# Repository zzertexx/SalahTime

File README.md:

# SalahTime
Device that shows prayer time and Qibla direction anywhere & anytime without any internet connection

## What is it?
It is an ESP32-powered device with buttons, GNSS receiver, RTC, magnetic sensor, and E-Paper display. By using all of these, it is planned to show prayer time using latitude and longitude alongside with direction to Qibla by magnetic sensor. Because there is an E-Paper display, battery can last for many-many days. If the battery will be drained, it is easy to charge using universal Type-C port. Currently, it shows prayer time based on location, but will have full interface and direction to Qibla in the future.

## Why did I build it?
I was walking in Shenzhen after Fallout with my phone died and then realized that I have to read Salah
I could not know if the next salah already started and I needed the direction to Qibla
Strangers there do not understand English, so I could not communicate with them
Then, I got an idea of internet-free device that can predict prayer time and show the direction to Qibla

## Steps to Reproduce
1. Order PCB and parts from any provider(Example: JLCPCB)
2. Assemble and solder parts to PCB
3. 3D Print CAD models from "CAD" folder
4. Push software into MCU and download required libraries using Arduino IDE 
5. Use!

## Arduino IDE Libraries:
GxEPD2
TinyGPS++
RTClib

## Bill of Materials
| Name | Quantity | Price |
| --- | --- | --- |
| DS3231M RTC | 1 | 3.25$ |
| ATGM336H GNSS | 1 | 2.22$ |
| ESP32-C3FH4 | 1 | 2.18$ |
| Vibration Motor | 1 | 0.56$ |
| Tactile Push Buttons | 5 | 0.3$ |
| Ceramic Active Antenna | 1 | 0.73$ |
| Coin Cell Holder | 1 | 1.27$ |
| MAX17048 fuel gauges | 1 | 2.18$ |
| ME6211 LDO to 3.3v | 1 | 0.52$ |
| NPN Transistor | 1 | 0.02$ |
| 2.9-inch E Ink Display | 1 | 4$ |
| 803040 1000 mAh LiPo | 1 | 4$ |
| Type-C 8 Pin | 1 | 0.04$ |
| 2.5mm JST Connector | 1 | 0.04$ |
| SI1308EDL N-MOSFET | 1 | 0.1$ |
| TP4056 | 1 | 0.2$ |
| FS8205A | 1 | 0.05$ |
| DW01A | 1 | 0.5$ |
| E Ink connector | 1 | 0.11$ |
| QST QMC5883P | 1 | 1.6$ | 
| 0,1uF C | 6 | 0.2$ |
| 10uF | 3 | 0.2$ | 
| 1uF/25V | 14 | 0.7$ |
| 4.7uF/25V | 3 | 0.2$ |
| 15pF | 2 | 0.03$ |
| 10nF | 1 | 0.02$ |
| THT 3mm diodes | 2 | 0.07$ |
| MBR0530 Diode | 3 | 0.02$ |
| 47nH L | 1 | 0,06$ |
| 47uH L | 1 | 0.08$ |
| 2nH L | 1 | 0.01$ |
| 10K R | 1 | 0.01$ |
| 1K R | 4 | 0.01$ |
| 1.2K R | 1 | 0.05$ |
| 4.7K R | 2 | 0.07$ |
| 100 R | 1 | 0.01$ |
| 1M R | 1 | 0.01$ |
| 2.2 R | 1 | 0.01$ |
| 499 R | 1 | 0.01$ |
| 0 R | 1 | 0.01$ |
| 10pF Crystal | 1 | 0.3$ | 
| TOTAL: | 26$ |

## Images

[schematics.pdf](https://github.com/user-attachments/files/32201017/schematics.pdf)

## AI DISCLOSURE
AI was used to search components and to write computing algorithm

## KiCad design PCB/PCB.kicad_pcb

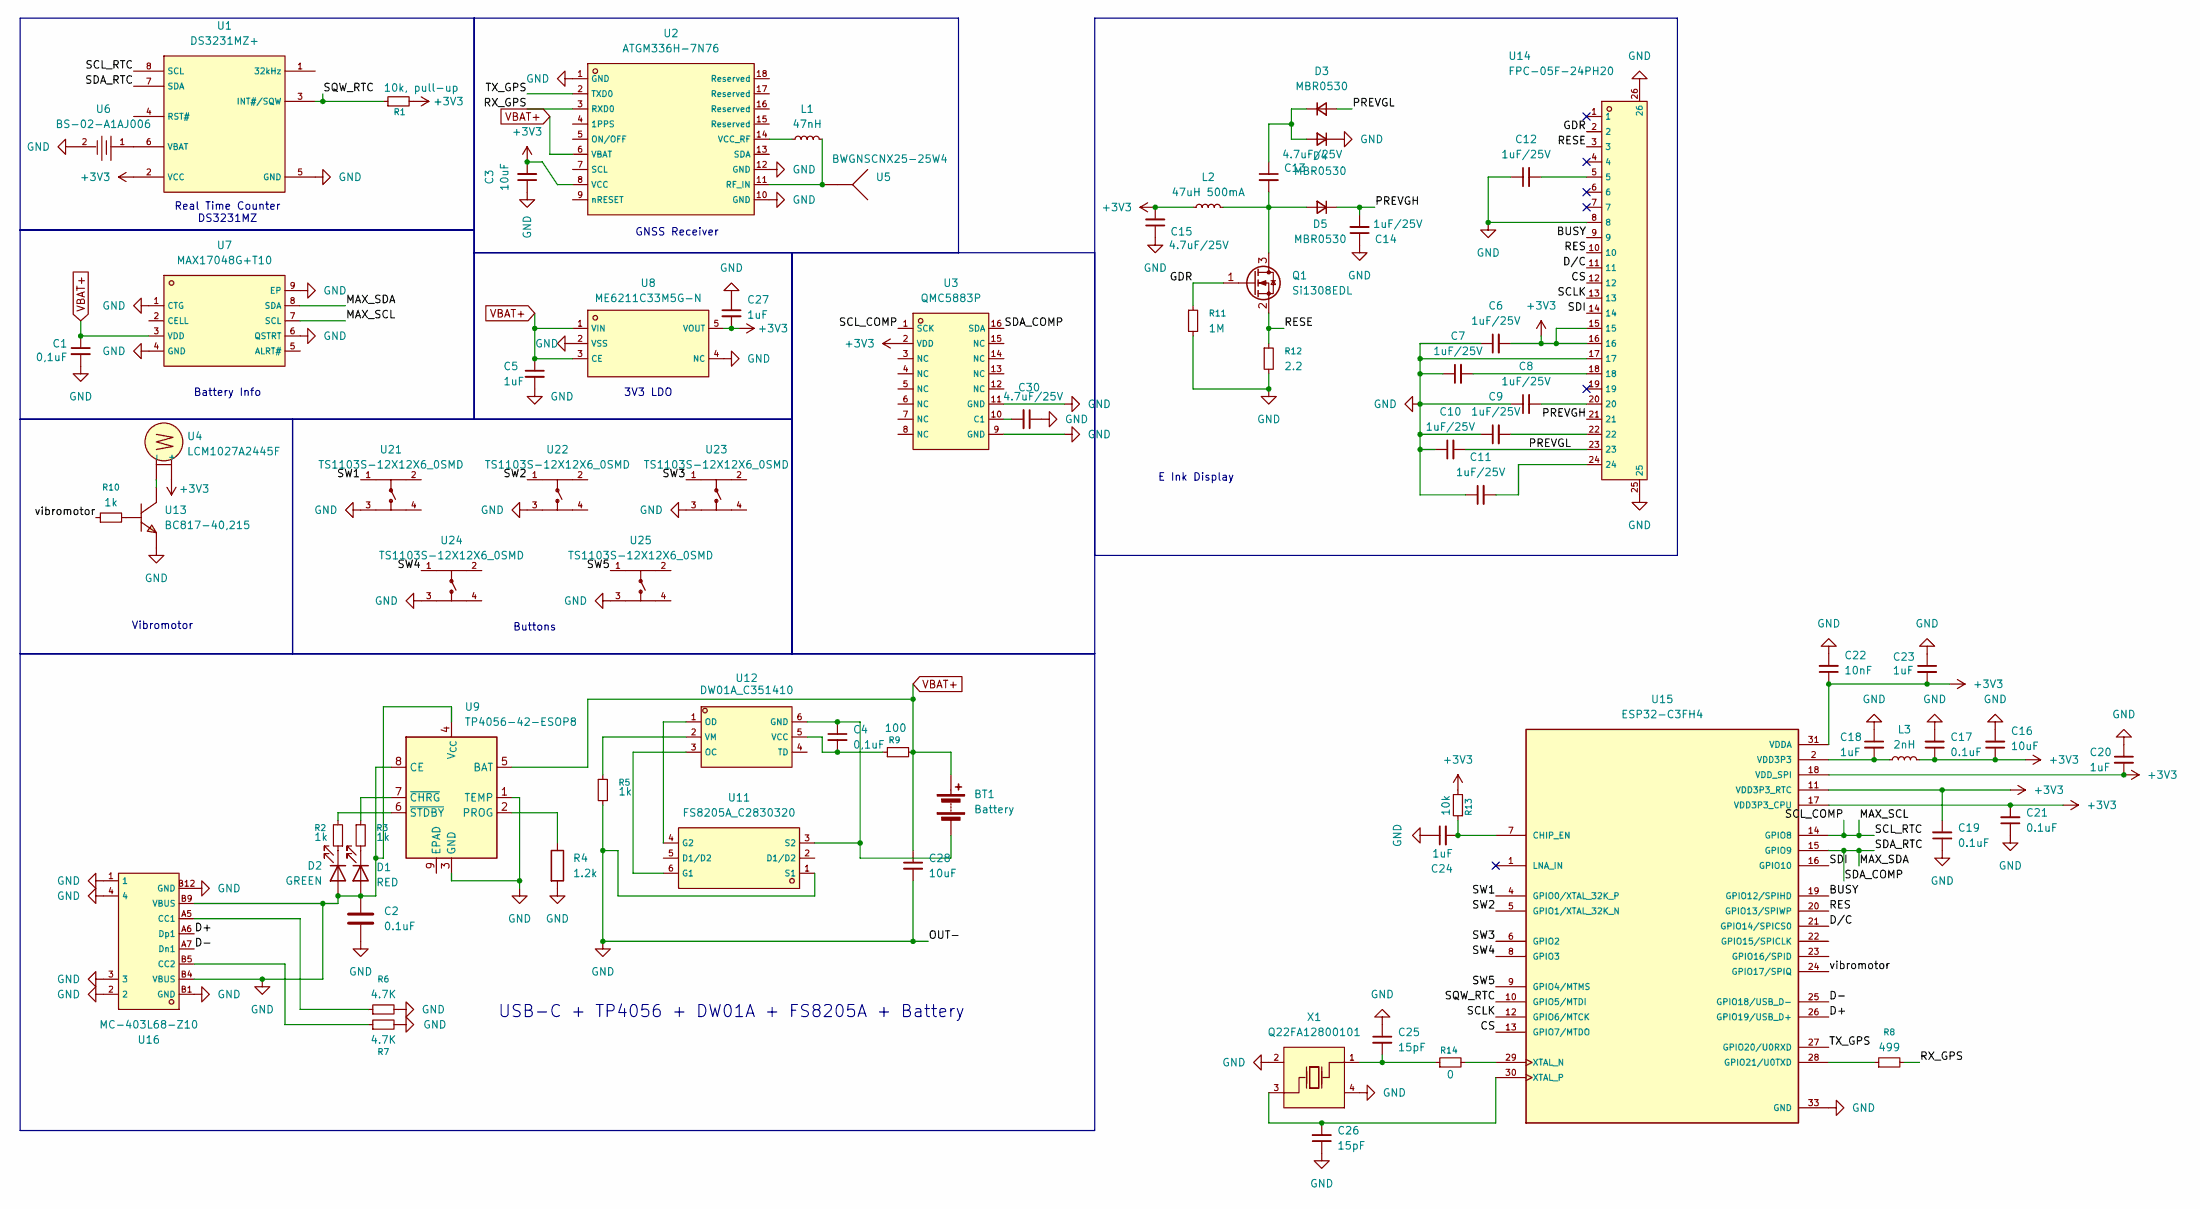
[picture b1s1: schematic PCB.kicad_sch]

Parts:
BT1: Battery; CONN-TH_S2B-XH-A-LF-SN
C1, C4: 0,1uF; C_0805_2012Metric_Pad1.18x1.45mm_HandSolder
C2, C17, C19, C21: 0.1uF; C_0805_2012Metric_Pad1.18x1.45mm_HandSolder
C3, C16, C28: 10uF; C_0805_2012Metric_Pad1.18x1.45mm_HandSolder
C5, C18, C20, C23, C24, C27: 1uF; C_0805_2012Metric_Pad1.18x1.45mm_HandSolder
C6, C7, C8, C9, C10, C11, C12, C14: 1uF/25V; C_0805_2012Metric_Pad1.18x1.45mm_HandSolder
C13, C15, C30: 4.7uF/25V; C_0805_2012Metric_Pad1.18x1.45mm_HandSolder
C22: 10nF; C_0603_1608Metric_Pad1.08x0.95mm_HandSolder
C25, C26: 15pF; C_0603_1608Metric_Pad1.08x0.95mm_HandSolder
D1: RED; LED_D3.0mm
D2: GREEN; LED_D3.0mm
D3, D4, D5: MBR0530; SOD-123_L2.7-W1.6-LS3.7-RD-1
L1: 47nH; L_0402_1005Metric_Pad0.77x0.64mm_HandSolder
L2: 47uH 500mA; IND-SMD_L4.0-W4.0_FNR40XXS
L3: 2nH; L_0603_1608Metric_Pad1.05x0.95mm_HandSolder
Q1: Si1308EDL; SOT-323_SC-70
R1: 10k, pull-up; R_0603_1608Metric_Pad0.98x0.95mm_HandSolder
R2, R3, R5, R10: 1k; R_0603_1608Metric_Pad0.98x0.95mm_HandSolder
R4: 1.2k; R_0603_1608Metric_Pad0.98x0.95mm_HandSolder
R6, R7: 4.7K; R_0603_1608Metric_Pad0.98x0.95mm_HandSolder
R8: 499; R_0603_1608Metric_Pad0.98x0.95mm_HandSolder
R9: 100; R_0805_2012Metric_Pad1.20x1.40mm_HandSolder
R11: 1M; R_0603_1608Metric_Pad0.98x0.95mm_HandSolder
R12: 2.2; R_0603_1608Metric_Pad0.98x0.95mm_HandSolder
R13: 10k; R_0603_1608Metric_Pad0.98x0.95mm_HandSolder
R14: 0; R_0603_1608Metric_Pad0.98x0.95mm_HandSolder
U1: DS3231MZ+; SOIC-8_L4.9-W3.9-P1.27-LS6.0-BL; LCSC C107410
U2: ATGM336H-7N76; COMM-SMD_18P-L10.1-W9.7-P1.1-TL_L76-LB; LCSC C53325902
U3: QMC5883P; LGA-16_L3.0-W3.0-P0.50-BL_SQ; LCSC C2847467
U4: LCM1027A2445F; VIBRATING-MOTOR-SMD_WELDING; LCSC C2759984
U5: BWGNSCNX25-25W4; ANT-TH_L25.0-W25.0; LCSC C784398
U6: BS-02-A1AJ006; BAT-TH_MYOUNG_BS-02-A1AJ006; LCSC C964745
U7: MAX17048G+T10; TDFN-8_L2.0-W2.0-P0.50-BL-EP1.2; LCSC C2682616
U8: ME6211C33M5G-N; SOT-23-5_L3.0-W1.7-P0.95-LS2.8-BL; LCSC C82942
U9: TP4056-42-ESOP8; SOIC-8-1EP_3.9x4.9mm_P1.27mm_EP2.41x3.3mm_ThermalVias
U11: FS8205A_C2830320; SOT-23-6_L2.9-W1.6-P0.95-LS2.8-BR; LCSC C2830320
U12: DW01A_C351410; SOT-23-6_L2.9-W1.6-P0.95-LS2.8-BL; LCSC C351410
U13: BC817-40,215; SOT-23-3_L2.9-W1.6-P1.90-LS2.8-BR; LCSC C52801
U14: FPC-05F-24PH20; FPC-SMD_24P-P0.50_FPC-05F-24PH20; LCSC C2856805
U15: ESP32-C3FH4; QFN50P500X500X90-33N; PARTREV 2.0
U16: MC-403L68-Z10; USB-TYPE-C-SMD_MC-403L68-Z10; LCSC C47326496
U21, U22, U23, U24, U25: TS1103S-12X12X6_0SMD; SW-SMD_4P-L12.0-W12.0-P5.00-LS15.5; LCSC C48677734
X1: Q22FA12800101; CRYSTAL-SMD_4P-L2.0-W1.6-BL; LCSC C255898

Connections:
+3V3: C3.2, C6.2, C15.2, C16.1, C17.1, C19.2, C20.2, C21.2, C22.1, C23.2, C27.2, L2.1, L3.2, R1.2, R13.2, U1.2 (VCC), U2.8 (VCC), U3.2 (VDD), U4.2 (+), U8.5 (VOUT), U14.15, U14.16, U15.11 (VDD3P3_RTC), U15.17 (VDD3P3_CPU), U15.18 (VDD_SPI), U15.31 (VDDA), U15.32 (VDDA)
/BUSY: U14.9, U15.19 (GPIO12/SPIHD)
/CS: U14.12, U15.13 (GPIO7/MTDO)
/D+: U15.26 (GPIO19/USB_D+), U16.A6 (Dp1)
/D-: U15.25 (GPIO18/USB_D-), U16.A7 (Dn1)
/D/C: U14.11, U15.21 (GPIO14/SPICS0)
/GDR: Q1.1 (G), R11.1, U14.2
/MAX_SCL: U1.8 (SCL), U3.1 (SCK), U7.7 (SCL), U15.14 (GPIO8)
/MAX_SDA: U1.7 (SDA), U3.16 (SDA), U7.8 (SDA), U15.15 (GPIO9)
/PREVGH: C14.2, D5.1 (K), U14.21
/PREVGL: C10.2, D3.2 (A), U14.23
/RES: U14.10, U15.20 (GPIO13/SPIWP)
/RESE: Q1.2 (S), R12.1, U14.3
/RX_GPS: R8.2, U2.3 (RXD0)
/SCLK: U14.13, U15.12 (GPIO6/MTCK)
/SDI: U14.14, U15.16 (GPIO10)
/SQW_RTC: R1.1, U1.3 (INT#/SQW), U15.10 (GPIO5/MTDI)
/SW1: U15.4 (GPIO0/XTAL_32K_P), U21.1
/SW2: U15.5 (GPIO1/XTAL_32K_N), U22.1
/SW3: U15.6 (GPIO2), U23.1
/SW4: U15.8 (GPIO3), U24.1
/SW5: U15.9 (GPIO4/MTMS), U25.1
/TX_GPS: U2.2 (TXD0), U15.27 (GPIO20/U0RXD)
/vibromotor: R10.1, U15.24 (GPIO17/SPIQ)
GND: C1.2, C2.1, C2.2, C3.1, C5.2, C6.1, C7.1, C8.1, C9.1, C10.1, C11.1, C12.1, C14.1, C15.1, C16.2, C17.2, C18.1, C19.1, C20.1, C21.1, C22.2, C23.1, C24.1, C25.1, C26.1, C27.1, C28.2, C30.1, D1.2 (A), D2.2 (A), D4.1 (K), R4.2, R5.2, R6.2, R7.2, R11.2, R12.2, U1.5 (GND), U2.1 (GND), U2.10 (GND), U2.12 (GND), U3.9 (GND), U3.11 (GND), U6.2, U7.1 (CTG), U7.4 (GND), U7.6 (QSTRT), U7.9 (EP), U8.2 (VSS), U8.4 (NC), U9.1 (TEMP), U9.3 (GND), U9.4 (V_{CC}), U9.8 (CE), U11.1 (S1), U13.2, U14.8, U14.17, U14.25, U14.26, U15.33 (GND), U16.1, U16.2, U16.3, U16.4, U16.B1 (GND), U16.B4 (VBUS), U16.B9 (VBUS), U16.B12 (GND), U21.3, U22.3, U23.3, U24.3, U25.3, X1.2, X1.4
unnamed: BT1.2 (-), C4.1, U11.3 (S2), U12.6 (GND)
unnamed: C7.2, U14.18
unnamed: C8.2, U14.20
unnamed: C9.2, U14.22
unnamed: C11.2, U14.24
unnamed: C12.2, U14.5
unnamed: D1.1 (K), R3.2
unnamed: D2.1 (K), R2.1
unnamed: C13.1, D3.1 (K), D4.2 (A)
unnamed: C13.2, D5.2 (A), L2.2, Q1.3 (D)
unnamed: R10.2, U13.1
unnamed: U1.6 (VBAT), U6.1
unnamed: L1.2, U2.11 (RF_IN), U5.1 (ANT_1)
unnamed: L1.1, U2.14 (VCC_RF)
unnamed: C30.2, U3.10 (C1)
unnamed: U4.1 (-), U13.3
unnamed: R4.1, U9.2 (PROG)
unnamed: R3.1, U9.7 (~CHRG)
unnamed: R2.2, U9.6 (~STDBY)
unnamed: U11.6 (G1), U12.3 (OC)
unnamed: U11.4 (G2), U12.1 (OD)
unnamed: C4.2, R9.1, U12.5 (VCC)
unnamed: R5.1, U12.2 (VM)
unnamed: C24.2, R13.1, U15.7 (CHIP_EN)
unnamed: R8.1, U15.28 (GPIO21/U0TXD)
unnamed: R14.2, U15.29 (XTAL_N)
unnamed: C26.2, U15.30 (XTAL_P), X1.3 (OSC2)
unnamed: R6.1, U16.A5 (CC1)
unnamed: R7.1, U16.B5 (CC2)
unnamed: C25.2, R14.1, X1.1 (OSC1)
VBAT+: BT1.1 (+), C1.1, C5.1, C28.1, R9.2, U2.6 (VBAT), U7.3 (VDD), U8.1 (VIN), U8.3 (CE), U9.5 (BAT)
VDD3P3: C18.2, L3.1, U15.2 (VDD3P3), U15.3 (VDD3P3)

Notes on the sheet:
3V3 LDO
Battery Info
Buttons
GNSS Receiver
Real Time Counter DS3231MZ
USB-C + TP4056 + DW01A + FS8205A + Battery
E Ink Display
Vibromotor

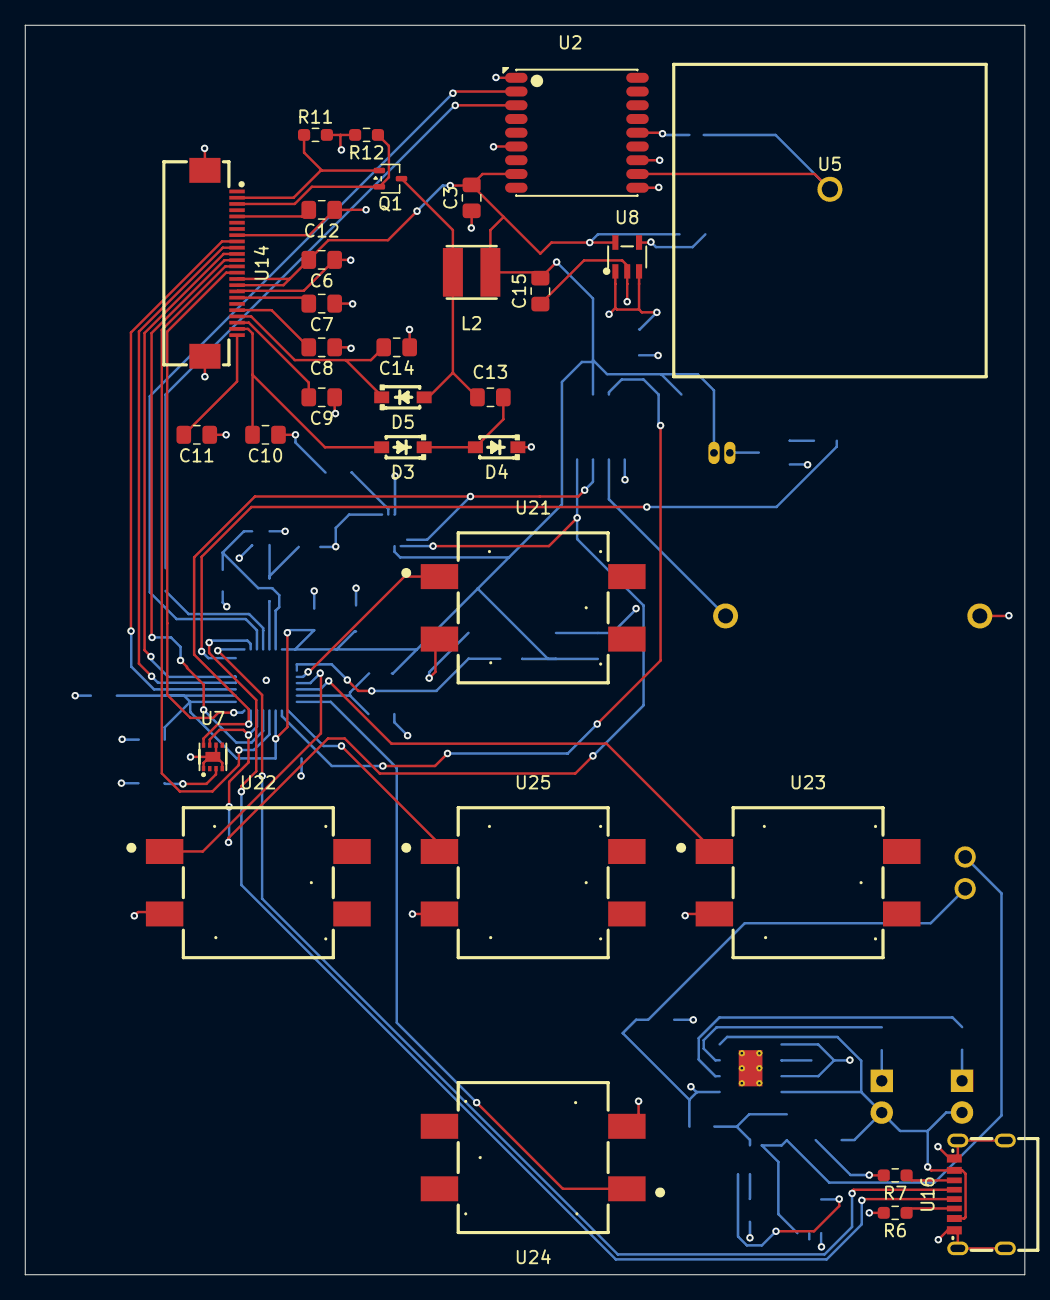
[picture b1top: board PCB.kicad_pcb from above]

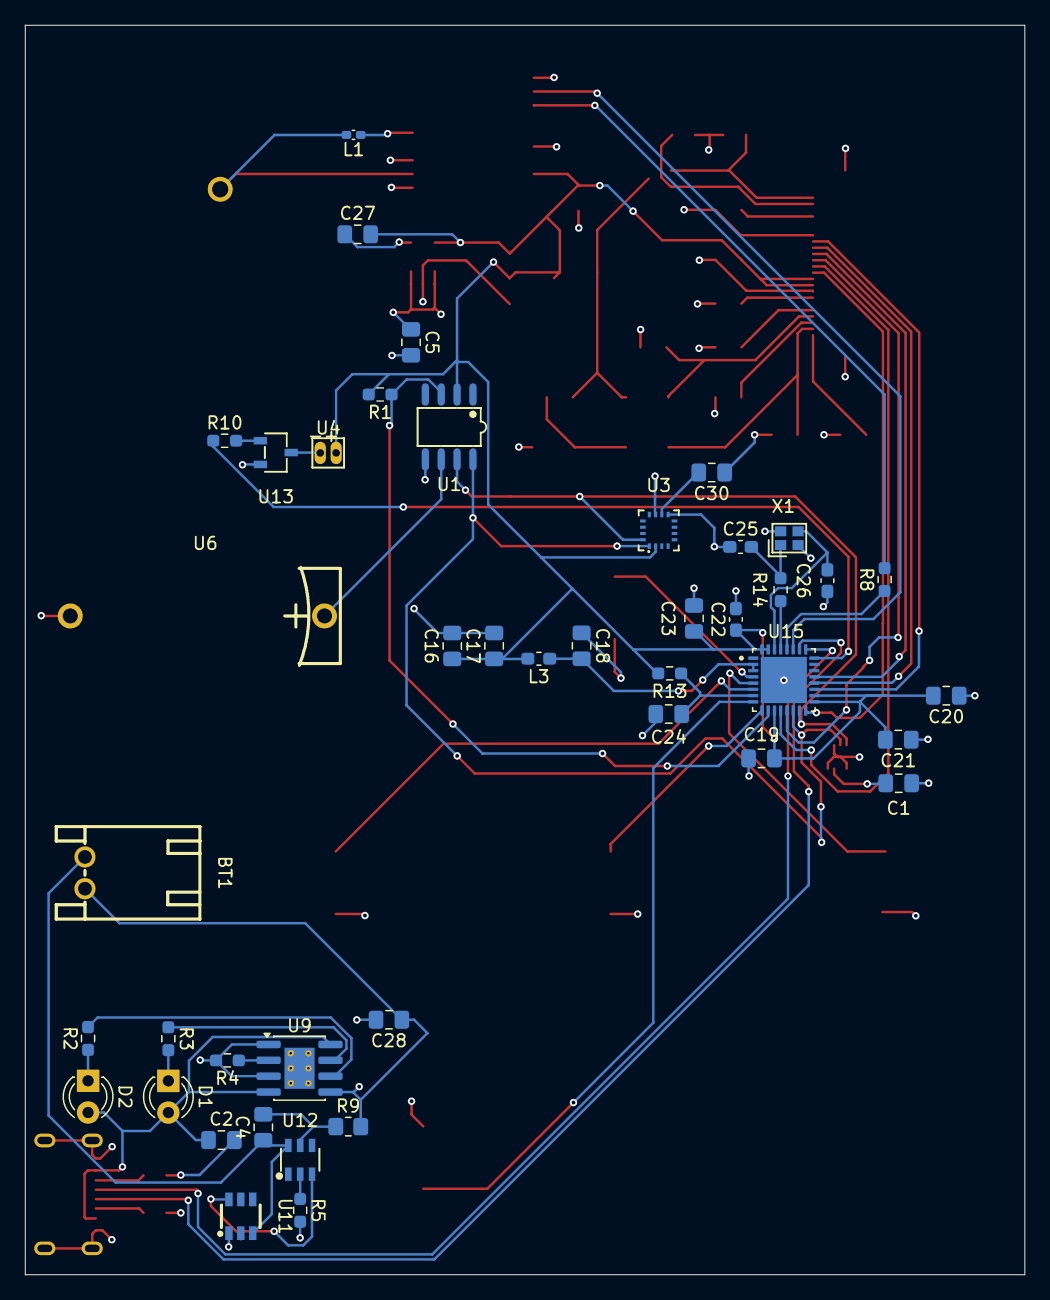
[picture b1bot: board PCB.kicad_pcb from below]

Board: 4 copper layers, 80.0 x 100.0 mm, 74 parts (43 on the bottom side), 57 nets.

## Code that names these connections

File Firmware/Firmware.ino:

#include <Wire.h>
#include <RTClib.h>
#include <TinyGPS++.h>
#include <GxEPD2_BW.h>
#include <Fonts/FreeMonoBold9pt7b.h>
#include <Preferences.h>
#include <math.h>

#define DEG2RAD(d) ((d) * M_PI / 180.0) 
#define RAD2DEG(r) ((r) * 180.0 / M_PI)

#define SW1 4
#define SW2 5
#define SW3 6
#define SW4 8
#define SW5 9
#define SQW_RTC 10  // INT#/SQW on DS3231
#define SCLK 12     // SCLK on E Ink screen connector
#define CS 13       // CS on E Ink screen connector
#define I2C_SCL 14
#define I2C_SDA 15
#define SDI 16         // SDI on E Ink screen
#define BUSY 19        // BUSY on E Ink screen
#define RES 20         // RES on E Ink screen
#define DC 21          // DC on E Ink screen
#define vibromotor 24  // base on transistor
#define TX_GPS 27
#define RX_GPS 28

const double FAJR_ANGLE = 18.0;
const double ISHA_ANGLE = 18.0;
const double ASR_FACTOR = 2;

struct PrayerTimes {
  double fajr, sunrise, dhuhr, asr, maghrib, isha;
};

double julianDay(int year, int month, int day) {
  if(month <= 2) { 
    year -= 1;
    month += 12;
  }
  int A = year / 100;
  int B = 2 - A + (A / 4);
  return floor(365.25 * (year + 4716)) + floor(30.6001 * (month + 1)) + day + B - 1524.5;
}

void sunPosition(double jd, double &declination, double &eqTimeMinutes) {
  double D = jd - 2451545.0;
  double g = fmod(357.529 + 0.98560028 * D, 360.0);
  double q = fmod(280.459 + 0.98564736 * D, 360.0);
  double L = fmod(q + 1.915 * sin(DEG2RAD(g)) + 0.020 * sin(DEG2RAD(2 * g)), 360.0);

  double e = 23.439 - 0.00000036 * D;

  double RA = RAD2DEG(atan2(cos(DEG2RAD(e)) * sin(DEG2RAD(L)), cos(DEG2RAD(L)))) / 15.0;
  RA = fmod(RA, 24.0);
  if (RA < 0) RA += 24.0; 

  declination = RAD2DEG(asin(sin(DEG2RAD(e)) * sin(DEG2RAD(L))));

  double eqTimeHours = (q / 15.0) - RA;

  if(eqTimeHours > 12) eqTimeHours -= 24;
  if(eqTimeHours < -12) eqTimeHours += 24;
  eqTimeMinutes = eqTimeHours * 60.0;
}

double hourAngle(double angle, double latitude, double declination) {
  double lat = DEG2RAD(latitude);
  double decl = DEG2RAD(declination);
  double a = DEG2RAD(angle);

  double cosH = (-sin(a) - sin(lat) * sin(decl)) / (cos(lat) * cos(decl));

  if (cosH > 1.0) cosH = 1.0;
  if (cosH < -1.0) cosH = -1.0;

  return RAD2DEG(acos(cosH)) / 15.0;
}

double asrHourAngle(double factor, double latitude, double declination) {
  double lat = DEG2RAD(latitude);
  double decl = DEG2RAD(declination);

  double a = -atan(1.0 / (factor + tan(fabs(lat - decl))));
  double cosH = (sin(a) - sin(lat) * sin(decl)) / (cos(lat) * cos(decl));

  if (cosH > 1.0) cosH = 1.0;
  if (cosH < -1.0) cosH = -1.0;

  return RAD2DEG(acos(cosH)) / 15.0;
}

PrayerTimes calculatePrayerTimes(int year, int month, int day, double latitude, double longitude, double timeZoneOffsetHours) {
  double jd = julianDay(year, month, day);

  double declination, eqTimeMinutes;
  sunPosition(jd, declination, eqTimeMinutes);
  double eqTimeHours = eqTimeMinutes / 60.0;

  double dhuhr = 12.0 + timeZoneOffsetHours - (longitude / 15.0) - eqTimeHours;

  double sunHA = hourAngle(0.833, latitude, declination);
  double fajrHA = hourAngle(FAJR_ANGLE, latitude, declination);
  double ishaHA = hourAngle(ISHA_ANGLE, latitude, declination);
  double asrHA = asrHourAngle(ASR_FACTOR, latitude, declination);

  PrayerTimes t;
  t.fajr = dhuhr - fajrHA;
  t.sunrise = dhuhr - sunHA;
  t.dhuhr = dhuhr;
  t.asr = dhuhr + asrHA;
  t.maghrib = dhuhr + sunHA;
  t.isha = dhuhr + ishaHA;

  return t;
}

void printTime(double decimalHours, char* buf, size_t bufSize) {
  if (decimalHours < 0) decimalHours += 24;
  if (decimalHours >= 24) decimalHours -= 24;
  int h = (int)decimalHours;
  int m = (int)round((decimalHours - h) * 60);
  if (m == 60) { m = 0; h += 1; }
  snprintf(buf, bufSize, "%02d:%02d", h, m);
}

// Objects
RTC_DS3231 rtc; // create an object "rtc" of type "RTC_DS3231"
TinyGPSPlus gps;
HardwareSerial gpsSerial(1);
Preferences prefs;

GxEPD2_BW<GxEPD2_290_T5, GxEPD2_290_T5::HEIGHT> display(
  GxEPD2_290_T5(CS, DC, RES, BUSY)
);

bool coldStart = false;

void showStatus(const char* msg) {
  display.setFullWindow();
  display.firstPage();
  do {
    display.fillScreen(GxEPD_WHITE);
    display.setCursor(10, 30);
    display.print(msg);
  } while (display.nextPage());
}

void acquireGpsFixBlocking() {
  unsigned long start = millis();
  bool locked = false;

  while(!locked) {
    while(gpsSerial.available() > 0) {
      gps.encode(gpsSerial.read());
    }

    if(gps.location.isValid() && gps.date.isValid() && gps.time.isValid()) {
      locked = true;

      double lat = gps.location.lat();
      double lng = gps.location.lng();

      rtc.adjust(DateTime(gps.date.year(), gps.date.month(), gps.date.day(), 
                          gps.time.hour(), gps.time.minute(), gps.time.second()));

      prefs.putFloat("lat", lat);
      prefs.putFloat("lng", lng);
      prefs.putBool("setup_done", true);

      Serial.printf("GPS Lock: %.6f, %.6f\n", lat, lng);
      showStatus("GPS Locked!");
      delay(1000);
    }

    if(millis() - start > 300000UL) {
      showStatus("No GPS fix. \nCheck sky view");
      delay(3000);
      start = millis();
    }
  }
}

void setup() {
  Serial.begin(115200);

  // Buttons as inputs
  pinMode(SW1, INPUT_PULLUP);
  pinMode(SW2, INPUT_PULLUP);
  pinMode(SW3, INPUT_PULLUP);
  pinMode(SW4, INPUT_PULLUP);
  pinMode(SW5, INPUT_PULLUP);

  // Vibration + short boot buzz
  pinMode(vibromotor, OUTPUT);
  digitalWrite(vibromotor, HIGH);
  delay(150);
  digitalWrite(vibromotor, LOW);

  // Screen on
  display.init(115200);
  display.setRotation(1);
  display.setFont(&FreeMonoBold9pt7b);
  display.setTextColor(GxEPD_BLACK);
  showStatus("Booting...");

  // I2C + RTC
  Wire.begin(I2C_SDA, I2C_SCL);
  pinMode(SQW_RTC, INPUT_PULLUP);

  if(!rtc.begin()) {
    Serial.println("DS3231 is not recognized!");
    showStatus("ERROR: RTC not found");
  }

  // NVS
  prefs.begin("salahtracker", false); // open a non-dependend on power memory inside of ESP32, false = write allowed
  bool setupComplete = prefs.getBool("setup_done", false);

  // Determine cold start
  bool timeInvalid = rtc.lostPower(); // true if the module lost power since the last check
  bool locationInvalid = !setupComplete;

  if(timeInvalid || locationInvalid){
    coldStart = true;
    Serial.println("COLD START - GPS FIX REQUIRED");
    showStatus("First time setup...\nSearching for GPS");
  } else {
    DateTime now = rtc.now();
    Serial.printf("Current RTC time is: %04d-%02d-%02d %02d:%02d\n", 
                    now.year(), now.month(), now.day(), now.hour(), now.minute());
  }

  gpsSerial.begin(9600, SERIAL_8N1, RX_GPS, TX_GPS);

  if(coldStart) {
    acquireGpsFixBlocking();
  }
  
  double tz = 5.0; // UTC +5

  PrayerTimes pt = calculatePrayerTimes(now.year(), now.month(), now.day(), lat, lng, tz);

  char fajrBuf[6], dhuhrBuf[6], asrBuf[6], maghribBuf[6], ishaBuf[6];
  printTime(pt.fajr, fajrBuf, sizeof(fajrBuf));
  printTime(pt.dhuhr, dhuhrBuf, sizeof(dhuhrBuf));
  printTime(pt.asr, asrBuf, sizeof(asrBuf));
  printTime(pt.maghrib, maghribBuf, sizeof(maghribBuf));
  printTime(pt.isha, ishaBuf, sizeof(ishaBuf));

  char buf(128);
  snprintf(buf, sizeof(buf), 
            "Fajr: %s\nDhuhr: %s\nAsr: %s\nMaghrib: %s\nIsha: %s", fajrBuf, dhuhrBuf, asrBuf, maghribBuf, ishaBuf)
  showStatus(buf);
}

void loop() {
  // put your main code here, to run repeatedly:
}
